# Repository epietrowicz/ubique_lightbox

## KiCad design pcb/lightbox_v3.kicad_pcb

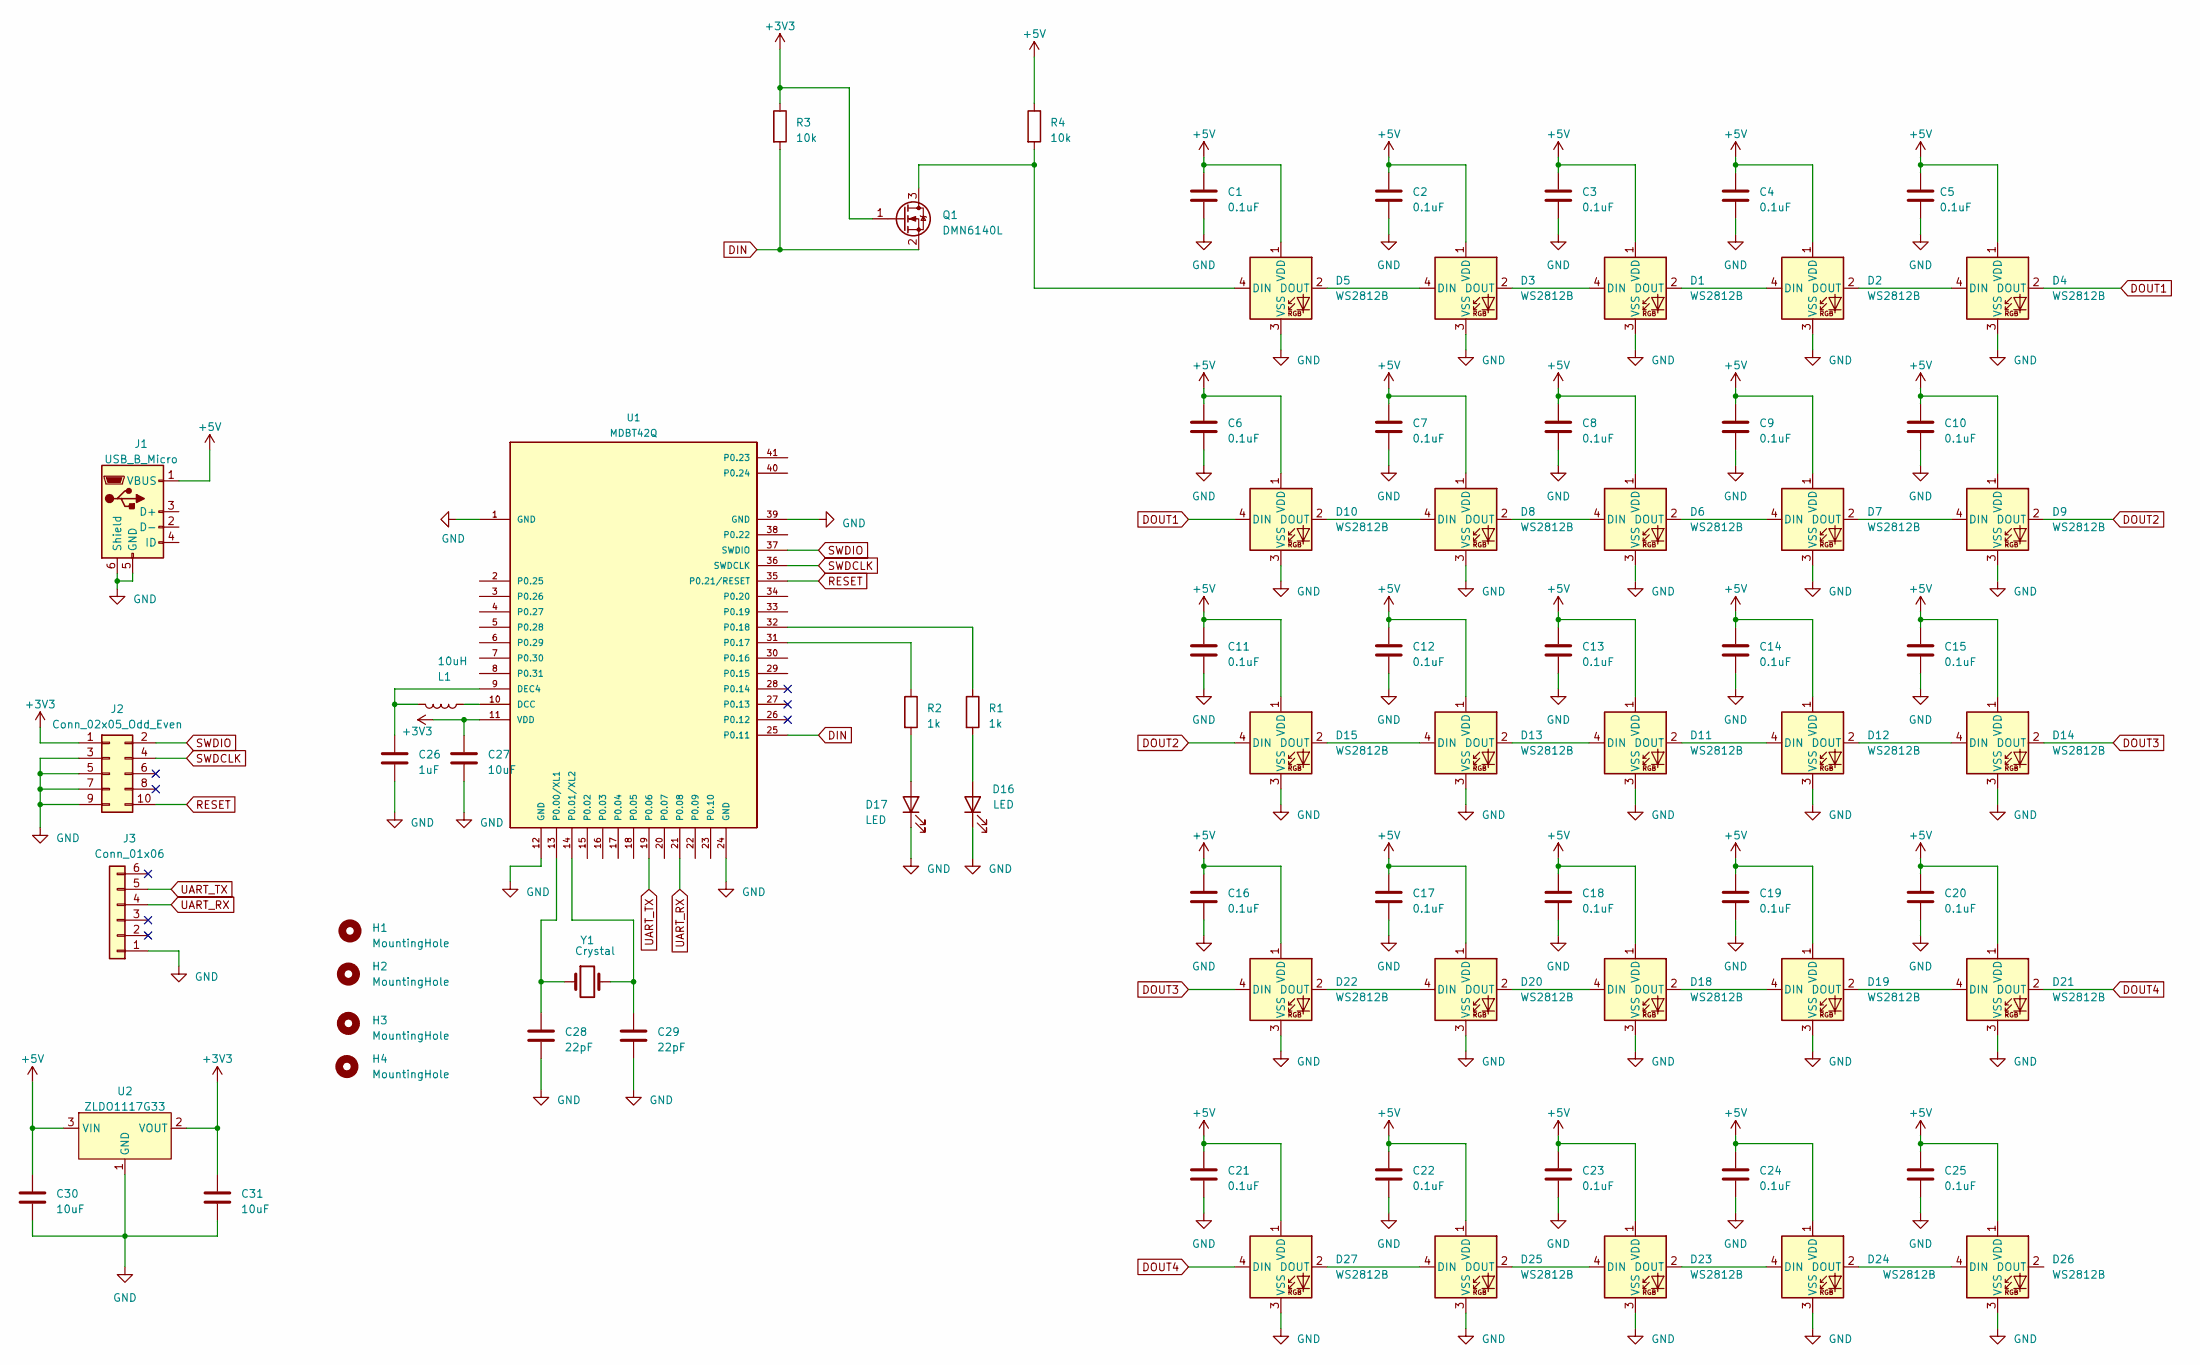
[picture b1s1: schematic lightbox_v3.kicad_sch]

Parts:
C1, C2, C3, C4, C5, C6, C7, C8, C9, C10, C11, C12, C13, C14, C15, C16, C17, C18, C19, C20, C21, C22, C23, C24, C25: 0.1uF; C_0603_1608Metric_Pad1.08x0.95mm_HandSolder
C26: 1uF; C_0603_1608Metric_Pad1.08x0.95mm_HandSolder
C27, C30, C31: 10uF; C_0603_1608Metric_Pad1.08x0.95mm_HandSolder
C28, C29: 22pF; C_0603_1608Metric_Pad1.08x0.95mm_HandSolder
D1, D2, D3, D4, D5, D6, D7, D8, D9, D10, D11, D12, D13, D14, D15, D18, D19, D20, D21, D22, D23, D24, D25, D26, D27: WS2812B; LED_WS2812B_PLCC4_5.0x5.0mm_P3.2mm
D16, D17: LED; LED_0603_1608Metric_Pad1.05x0.95mm_HandSolder
H1, H2, H3, H4: MountingHole; MountingHole_3.2mm_M3
J1: USB_B_Micro; USB_Micro-B_Amphenol_10103594-0001LF_Horizontal
J2: Conn_02x05_Odd_Even; PinHeader_2x05_P1.27mm_Vertical_SMD
J3: Conn_01x06; PinHeader_1x06_P2.54mm_Vertical
L1: 10uH; L_0805_2012Metric_Pad1.15x1.40mm_HandSolder
Q1: DMN6140L; SOT-23
R1, R2: 1k; R_0603_1608Metric_Pad0.98x0.95mm_HandSolder
R3, R4: 10k; R_0603_1608Metric_Pad0.98x0.95mm_HandSolder
U1: MDBT42Q
U2: ZLDO1117G33; SOT-223-3_TabPin2
Y1: Crystal; Crystal_C38-LF_D3.0mm_L8.0mm_Horizontal

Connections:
+3V3: C27.1, C31.1, J2.1, Q1.1 (G), R3.1, U1.11 (VDD), U2.2 (VOUT)
+5V: C1.1, C2.1, C3.1, C4.1, C5.1, C6.1, C7.1, C8.1, C9.1, C10.1, C11.1, C12.1, C13.1, C14.1, C15.1, C16.1, C17.1, C18.1, C19.1, C20.1, C21.1, C22.1, C23.1, C24.1, C25.1, C30.1, D1.1 (VDD), D2.1 (VDD), D3.1 (VDD), D4.1 (VDD), D5.1 (VDD), D6.1 (VDD), D7.1 (VDD), D8.1 (VDD), D9.1 (VDD), D10.1 (VDD), D11.1 (VDD), D12.1 (VDD), D13.1 (VDD), D14.1 (VDD), D15.1 (VDD), D18.1 (VDD), D19.1 (VDD), D20.1 (VDD), D21.1 (VDD), D22.1 (VDD), D23.1 (VDD), D24.1 (VDD), D25.1 (VDD), D26.1 (VDD), D27.1 (VDD), J1.1 (VBUS), R4.1, U2.3 (VIN)
DIN: Q1.2 (S), R3.2, U1.25 (P0.11)
DOUT1: D4.2 (DOUT), D10.4 (DIN)
DOUT2: D9.2 (DOUT), D15.4 (DIN)
DOUT3: D14.2 (DOUT), D22.4 (DIN)
DOUT4: D21.2 (DOUT), D27.4 (DIN)
GND: C1.2, C2.2, C3.2, C4.2, C5.2, C6.2, C7.2, C8.2, C9.2, C10.2, C11.2, C12.2, C13.2, C14.2, C15.2, C16.2, C17.2, C18.2, C19.2, C20.2, C21.2, C22.2, C23.2, C24.2, C25.2, C26.2, C27.2, C28.2, C29.2, C30.2, C31.2, D1.3 (VSS), D2.3 (VSS), D3.3 (VSS), D4.3 (VSS), D5.3 (VSS), D6.3 (VSS), D7.3 (VSS), D8.3 (VSS), D9.3 (VSS), D10.3 (VSS), D11.3 (VSS), D12.3 (VSS), D13.3 (VSS), D14.3 (VSS), D15.3 (VSS), D16.1 (K), D17.1 (K), D18.3 (VSS), D19.3 (VSS), D20.3 (VSS), D21.3 (VSS), D22.3 (VSS), D23.3 (VSS), D24.3 (VSS), D25.3 (VSS), D26.3 (VSS), D27.3 (VSS), J1.5 (GND), J1.6 (Shield), J2.3, J2.5, J2.7, J2.9, J3.1, U1.1 (GND), U1.12 (GND), U1.24 (GND), U1.39 (GND), U2.1 (GND)
unnamed: C26.1, L1.2, U1.9 (DEC4)
unnamed: C28.1, U1.13 (P0.00/XL1), Y1.1
unnamed: C29.1, U1.14 (P0.01/XL2), Y1.2
unnamed: D1.2 (DOUT), D2.4 (DIN)
unnamed: D1.4 (DIN), D3.2 (DOUT)
unnamed: D2.2 (DOUT), D4.4 (DIN)
unnamed: D3.4 (DIN), D5.2 (DOUT)
unnamed: D5.4 (DIN), Q1.3 (D), R4.2
unnamed: D6.2 (DOUT), D7.4 (DIN)
unnamed: D6.4 (DIN), D8.2 (DOUT)
unnamed: D7.2 (DOUT), D9.4 (DIN)
unnamed: D8.4 (DIN), D10.2 (DOUT)
unnamed: D11.2 (DOUT), D12.4 (DIN)
unnamed: D11.4 (DIN), D13.2 (DOUT)
unnamed: D12.2 (DOUT), D14.4 (DIN)
unnamed: D13.4 (DIN), D15.2 (DOUT)
unnamed: D16.2 (A), R1.2
unnamed: D17.2 (A), R2.2
unnamed: D18.2 (DOUT), D19.4 (DIN)
unnamed: D18.4 (DIN), D20.2 (DOUT)
unnamed: D19.2 (DOUT), D21.4 (DIN)
unnamed: D20.4 (DIN), D22.2 (DOUT)
unnamed: D23.2 (DOUT), D24.4 (DIN)
unnamed: D23.4 (DIN), D25.2 (DOUT)
unnamed: D24.2 (DOUT), D26.4 (DIN)
unnamed: D25.4 (DIN), D27.2 (DOUT)
unnamed: L1.1, U1.10 (DCC)
unnamed: R1.1, U1.32 (P0.18)
unnamed: R2.1, U1.31 (P0.17)
RESET: J2.10, U1.35 (P0.21/RESET)
SWDCLK: J2.4, U1.36 (SWDCLK)
SWDIO: J2.2, U1.37 (SWDIO)
UART_RX: J3.4, U1.21 (P0.08)
UART_TX: J3.5, U1.19 (P0.06)

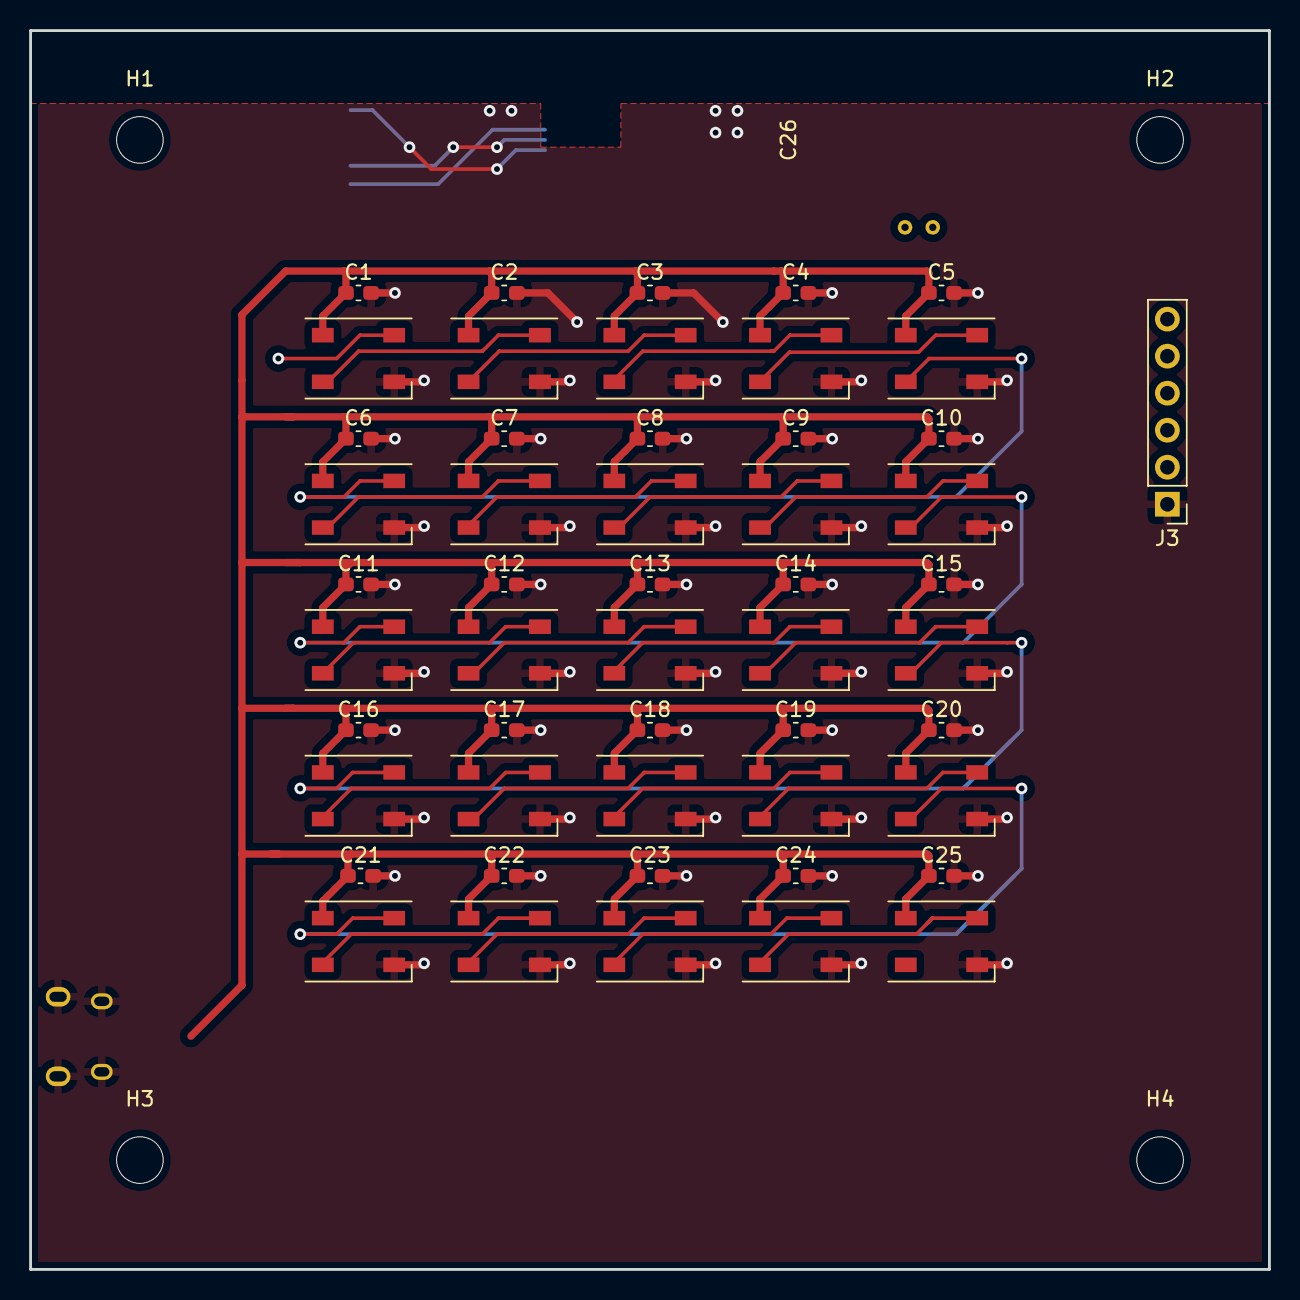
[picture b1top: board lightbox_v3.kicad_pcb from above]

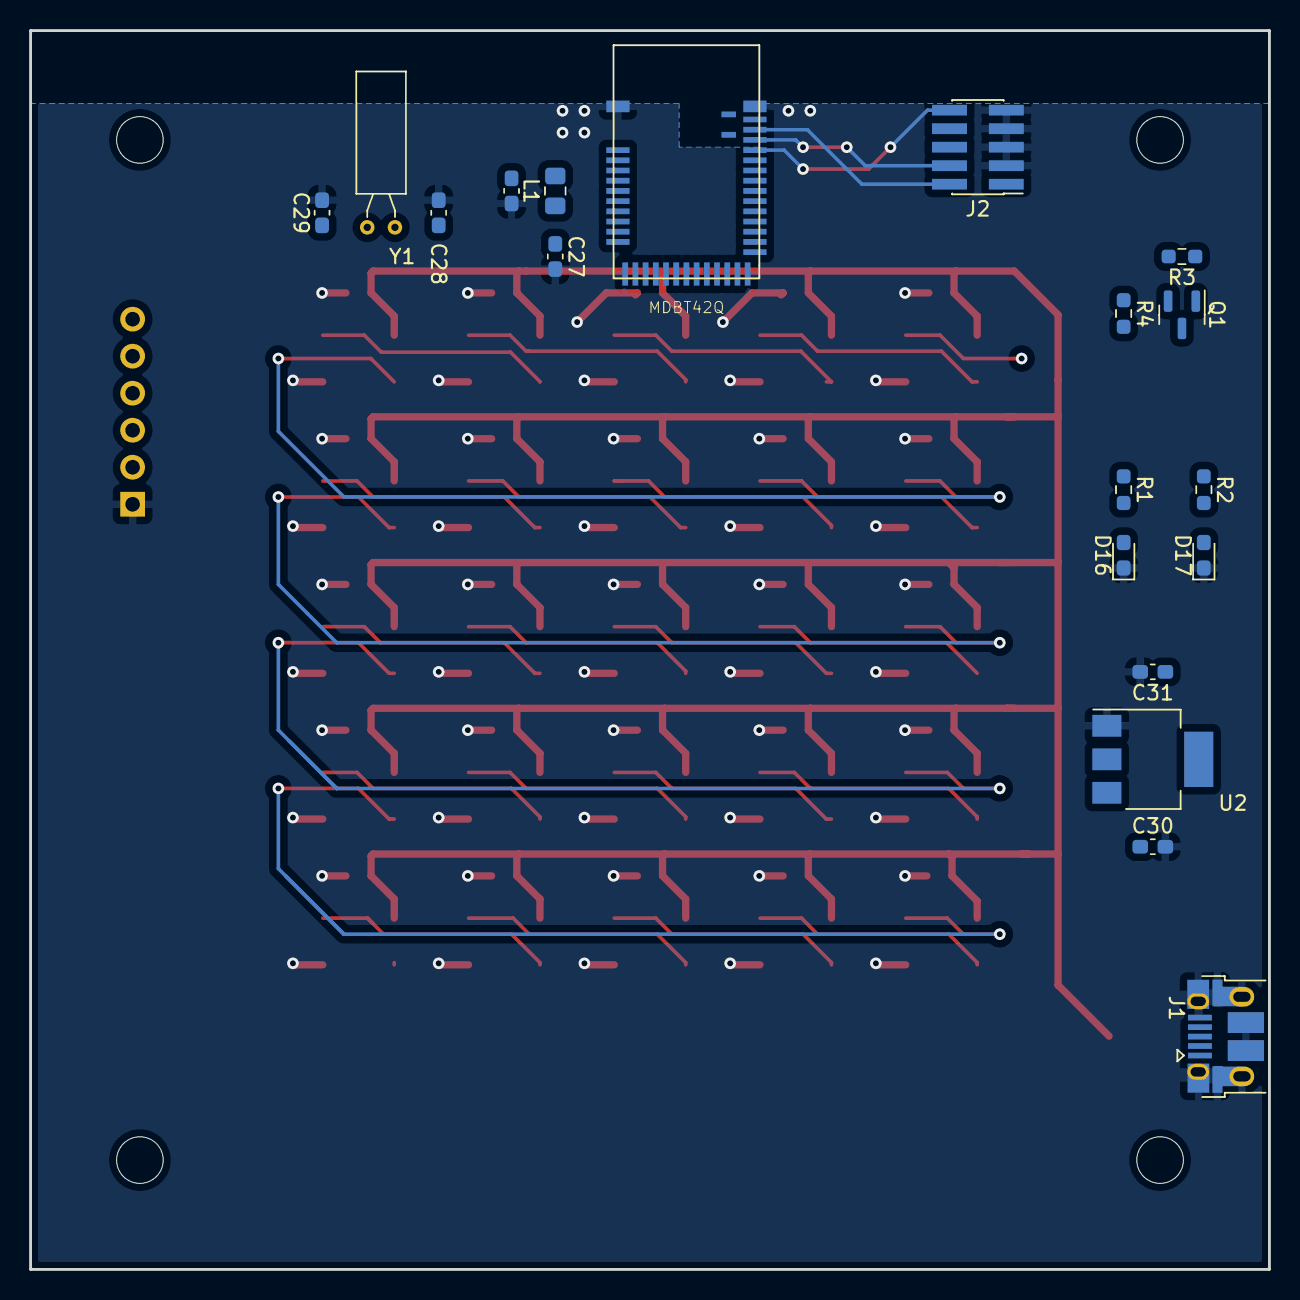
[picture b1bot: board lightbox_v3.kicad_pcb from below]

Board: 2 copper layers, 85.0 x 85.0 mm, 74 parts (19 on the bottom side), 42 nets.

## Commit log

2021-08-06 inital commit
